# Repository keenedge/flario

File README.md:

# FLARIO

## Windows Dev Config

ESP32 plugin to a local com port. (COM10)

A a TASkSchd task
- At System Startup
- Program: "C:\Program Files (x86)\com0com\hub4com.exe"
- Args: --baud=115200 \\.\COM10 --use-driver=tcp 7000

## MX Linux dev config

/etc/systemd/system/ttyVCOM0

   [Unit]
   Description=ESP32 TCP to TTY Bridge (/dev/ttyVCOM0)
   After=network-online.target
   Wants=network-online.target

   [Service]
   Type=simple
   ExecStart=/usr/bin/socat \
     pty,raw,echo=0,link=/dev/ttyVCOM0,mode=666,b115200 \
     tcp:10.0.0.8:7000,retry=1000000,interval=1
   Restart=always
   RestartSec=1

   [Install]
   WantedBy=multi-user.target

### Restart Service
sudo systemctl daemon-reload
sudo systemctl restart ttyvcom0.service

### Test

   screen /dev/ttyVCOM0

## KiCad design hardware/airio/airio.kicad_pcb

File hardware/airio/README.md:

# airio

KiCad project for the airio carrier board: a Seeed XIAO nRF52840 soldered on
as a castellated module, with a BMP581 barometer, an LSM6DSV16X IMU, a piezo
beeper, a button, a 1S LiPo connector and SWD test pads. Signals follow the
pin map in [docs/airio-parts-and-pinmap.md](../../docs/airio-parts-and-pinmap.md).

Open `airio.kicad_pro` in KiCad 10. All files are saved in the KiCad 10
format. `airio.pdf` is a plot of the current schematic for reading without
KiCad.

| File | Contents |
|---|---|
| `airio.kicad_sch` | Schematic, one A4 sheet |
| `airio.kicad_pcb` | Two-layer board, 1.0 mm thick: layout and routing in progress |
| `airio.kicad_dru` | Custom DRC rules (see PCB below) |
| `airio-top.png` | Render of an earlier placement |
| `airio.kicad_sym` | Project symbols: XIAO nRF52840, BMP581, LSM6DSV16X |
| `airio.pretty/` | Project footprints: `XIAO-nRF52840-SMD`, `Bosch_LGA-10_2x2mm_P0.5mm` |
| `sym-lib-table`, `fp-lib-table` | Add the two project libraries as `airio` |
| `airio.pdf` | Schematic plot |

## ERC

ERC in KiCad 10.0.7 reports 0 errors and 2 warnings. Both warnings are
sensor address straps tied to a supply rail, which is intended:

- U2 (BMP581) SDO to +3V3 selects I2C address 0x47.
- U3 (LSM6DSV16X) SDO/SA0 to GND selects I2C address 0x6A.

Exclude them in the ERC window (right-click, Exclude) if you want a clean run.

## Footprints

- **U1** uses Seeed's `XIAO-nRF52840-SMD` footprint from
  [Seeed-Studio/OPL_Kicad_Library](https://github.com/Seeed-Studio/OPL_Kicad_Library)
  (commit 3be8215, CC-BY-SA-4.0). Pads 1-14 are the castellated edge, 15-18 the
  underside SWD pads (SWDIO, SWCLK, RST, GND), 19-20 the battery pads (BAT+,
  BAT-) and 21-22 NFC1/NFC2. The project symbol's underside pins were
  renumbered to Seeed's order so they land on the right pads.
- **U2** uses `Bosch_LGA-10_2x2mm_P0.5mm`: 10 pads at 0.5 mm pitch, two on the
  pin 1 side and three on each adjacent side, numbered counter-clockwise from
  the top. Pad centres sit 0.775 mm from the body centre, pads are 0.30 x
  0.325 mm. It was cross-checked against four open-source BMP581 footprints,
  since Bosch's datasheet PDF couldn't be read here. Check it against
  section 8 of the datasheet before ordering. The BMP580 uses the same package.

Every symbol pin has a matching footprint pad (checked with KiCad's pcbnew
Python against the netlist).

## Display options

J3 is a cable port for a display breakout (Sharp memory LCD, or an ST7305
adapter). J6 is an on-board 24-pin 0.5 mm FPC for a bare 2.9" 168x384 ST7305
reflective panel (Osptek YDP290H001-V3, Good Display GDTL029T51), with its
seven 1 µF capacitors C6-C12. Both share SCR_CLK, SCR_MOSI, SCR_CS, SCR_DISP
(ST7305 RES) and SCR_DC (D8). Fit one display at a time.

J6's footprint is a placeholder (`Hirose_FH12-24S-0.5SH`): check the pads
against the HCTL HC-FPC-05-09-24RLTAG drawing before layout. The J6 pinout and
capacitor values come from search extracts of the panel spec, not the PDF
itself; confirm them too. `airio.pdf` has not been re-plotted for J6.

## PCB

- **Size:** 54 x 24 mm, two layers, 1.0 mm FR4. SMD parts sit on the top side
  for single-sided JLC reflow. J2-J5 are SMD JST SH, so the
  whole board can be reflowed. The six bare test pads are on the bottom.
- **Placement and routing:** being re-laid out and routed by hand in KiCad (work
  in progress). `airio-top.png` shows the earlier scripted placement, not the
  current layout. The antenna keepout rule area and the custom rules stay.
- **Test pads:** TP1-TP6 are on the bottom in a 2.54 mm row (GND, 3V3, SWDIO,
  SWCLK, RST, VBAT, left to right seen from the top), under the battery, for a
  pogo-pin SWD adapter.
- **DRC:** KiCad 10.0.7 with schematic parity finds no footprint or parity
  errors. `airio.kicad_dru` allows the 0.15 mm pad gaps of ST's LGA-14 land
  pattern, sets a 0.3 mm copper-to-edge clearance, and allows 0.15 mm tracks,
  all within JLC's standard limits.

## Parts

Prices are LCSC, converted at 1.3993 CAD per USD (Bank of Canada, 2026-10-23),
excluding shipping and duty. Stock was read from LCSC's product API on
2026-10-24, on 2026-10-25 for U2, U4 and R3/R4, and on 2026-10-26 for J2-J5. "Each" is the price at LCSC's smallest order quantity.

| Ref | Part | LCSC # | Qty | CAD each | Min order | LCSC stock |
|---|---|---|---|---|---|---|
| U1 | Seeed XIAO nRF52840 (102010448) | [C17209540](https://www.lcsc.com/product-detail/C17209540.html) | 1 | C$15.18 | 1 | 158 |
| U2 | Bosch BMP581 | [C5362283](https://www.lcsc.com/product-detail/C5362283.html) | 1 | C$3.41 | 1 | 7,388 |
| U2 alt | Bosch BMP580 | [C22391138](https://www.lcsc.com/product-detail/C22391138.html) | 1 | C$1.70 | 1 | 14,944 |
| U3 | ST LSM6DSV16XTR | [C5267406](https://www.lcsc.com/product-detail/C5267406.html) | 1 | C$4.75 | 1 | 6,395 |
| J1 | JST S2B-PH-K-S(LF)(SN), 2-pin PH side-entry THT, on the back | [C173752](https://www.lcsc.com/product-detail/C173752.html) | 1 | C$0.056 | 20 | 202,040 |
| J2, J4 | JST SM04B-SRSS-TB(LF)(SN), 4-pin SH side-entry SMD | [C160404](https://www.lcsc.com/product-detail/C160404.html) | 2 | C$0.303 | 5 | 63,590 |
| J3 | JST SM08B-SRSS-TB(LF)(SN), 8-pin SH side-entry SMD | [C160407](https://www.lcsc.com/product-detail/C160407.html) | 1 | C$0.457 | 5 | 194,320 |
| J5 | JST SM02B-SRSS-TB(LF)(SN), 2-pin SH side-entry SMD (buzzer) | [C160402](https://www.lcsc.com/product-detail/C160402.html) | 1 | C$0.187 | 5 | 73,300 |
| SW1 | XKB TS-1187A-B-A-B | [C318884](https://www.lcsc.com/product-detail/C318884.html) | 1 | C$0.03 | 20 | 923,940 |
| C1-C4 | Samsung CL10B104KO8NNNC, 100 nF 16 V X7R 0603 | [C66501](https://www.lcsc.com/product-detail/C66501.html) | 4 | C$0.013 | 50 | 796,150 |
| R1, R2 | UNI-ROYAL 0603WAF4701T5E, 4.7 kΩ 0603 | [C23162](https://www.lcsc.com/product-detail/C23162.html) | 2 | C$0.004 | 100 | 4,646,400 |
| U4 | TI TCA9534PWR I/O expander, TSSOP-16 | [C783615](https://www.lcsc.com/product-detail/C783615.html) | 1 | C$1.31 | 1 | 11,270 |
| R3, R4 | UNI-ROYAL 0603WAF1002T5E, 10 kΩ 0603 | [C25804](https://www.lcsc.com/product-detail/C25804.html) | 2 | C$0.003 | 100 | 567,800 |
| C5 | Samsung CL10B104KO8NNNC, 100 nF 16 V X7R 0603 | [C66501](https://www.lcsc.com/product-detail/C66501.html) | 1 | C$0.013 | 50 | 796,150 |

Ports J2-J4 follow `/mnt/project-files/airio/core-ports-spec.md`: pin 1 is GND on
all of them. J2-J5 are JST SH (1.0 mm) side-entry SMD, so JLC can reflow them; they
need to sit at the board edge, and SH leads are best bought pre-crimped. J4 matches the
Qwiic / STEMMA QT pinout. The buzzer is off-board on J5. The NFC pads sit inside the
antenna keepout, so they are unused. U4, a TCA9534 I2C expander at 0x20, carries BTN
(P3), BARO_INT (P0), SCR_DISP (P2) and IMU_INT1 (P1); its INT output on D5 wakes the
XIAO from System OFF. See the pin map for the XIAO pin assignment.

C1-C4 were changed from C1591 to C66501 because C1591 shows 0 stock at LCSC.
The BMP581 is back in stock at LCSC (2026-10-25); the BMP580 still fits the same footprint as a fallback.

## J1 on the back

J1 is a through-hole JST PH (S2B-PH-K-S) mounted on the bottom side, so the
battery lead runs along the back. Hand solder it from the top after JLC's
single-sided assembly, and mark it "do not place" in the JLC BOM. Its pins
poke about 1.5 mm through the top side, so keep those spots clear.

## Still to do before ordering

- Check J1's polarity against the LiPo you'll use. Pin 1 is VBAT. JST PH
  battery packs are not consistent about which side is red.
- Check the BMP581 footprint against section 8 of the datasheet.

To point the KiCad MCP server at this project, set
`KICAD_MCP_PROJECT_DIR=hardware/airio` or ask Claude to call `kicad_set_project`.

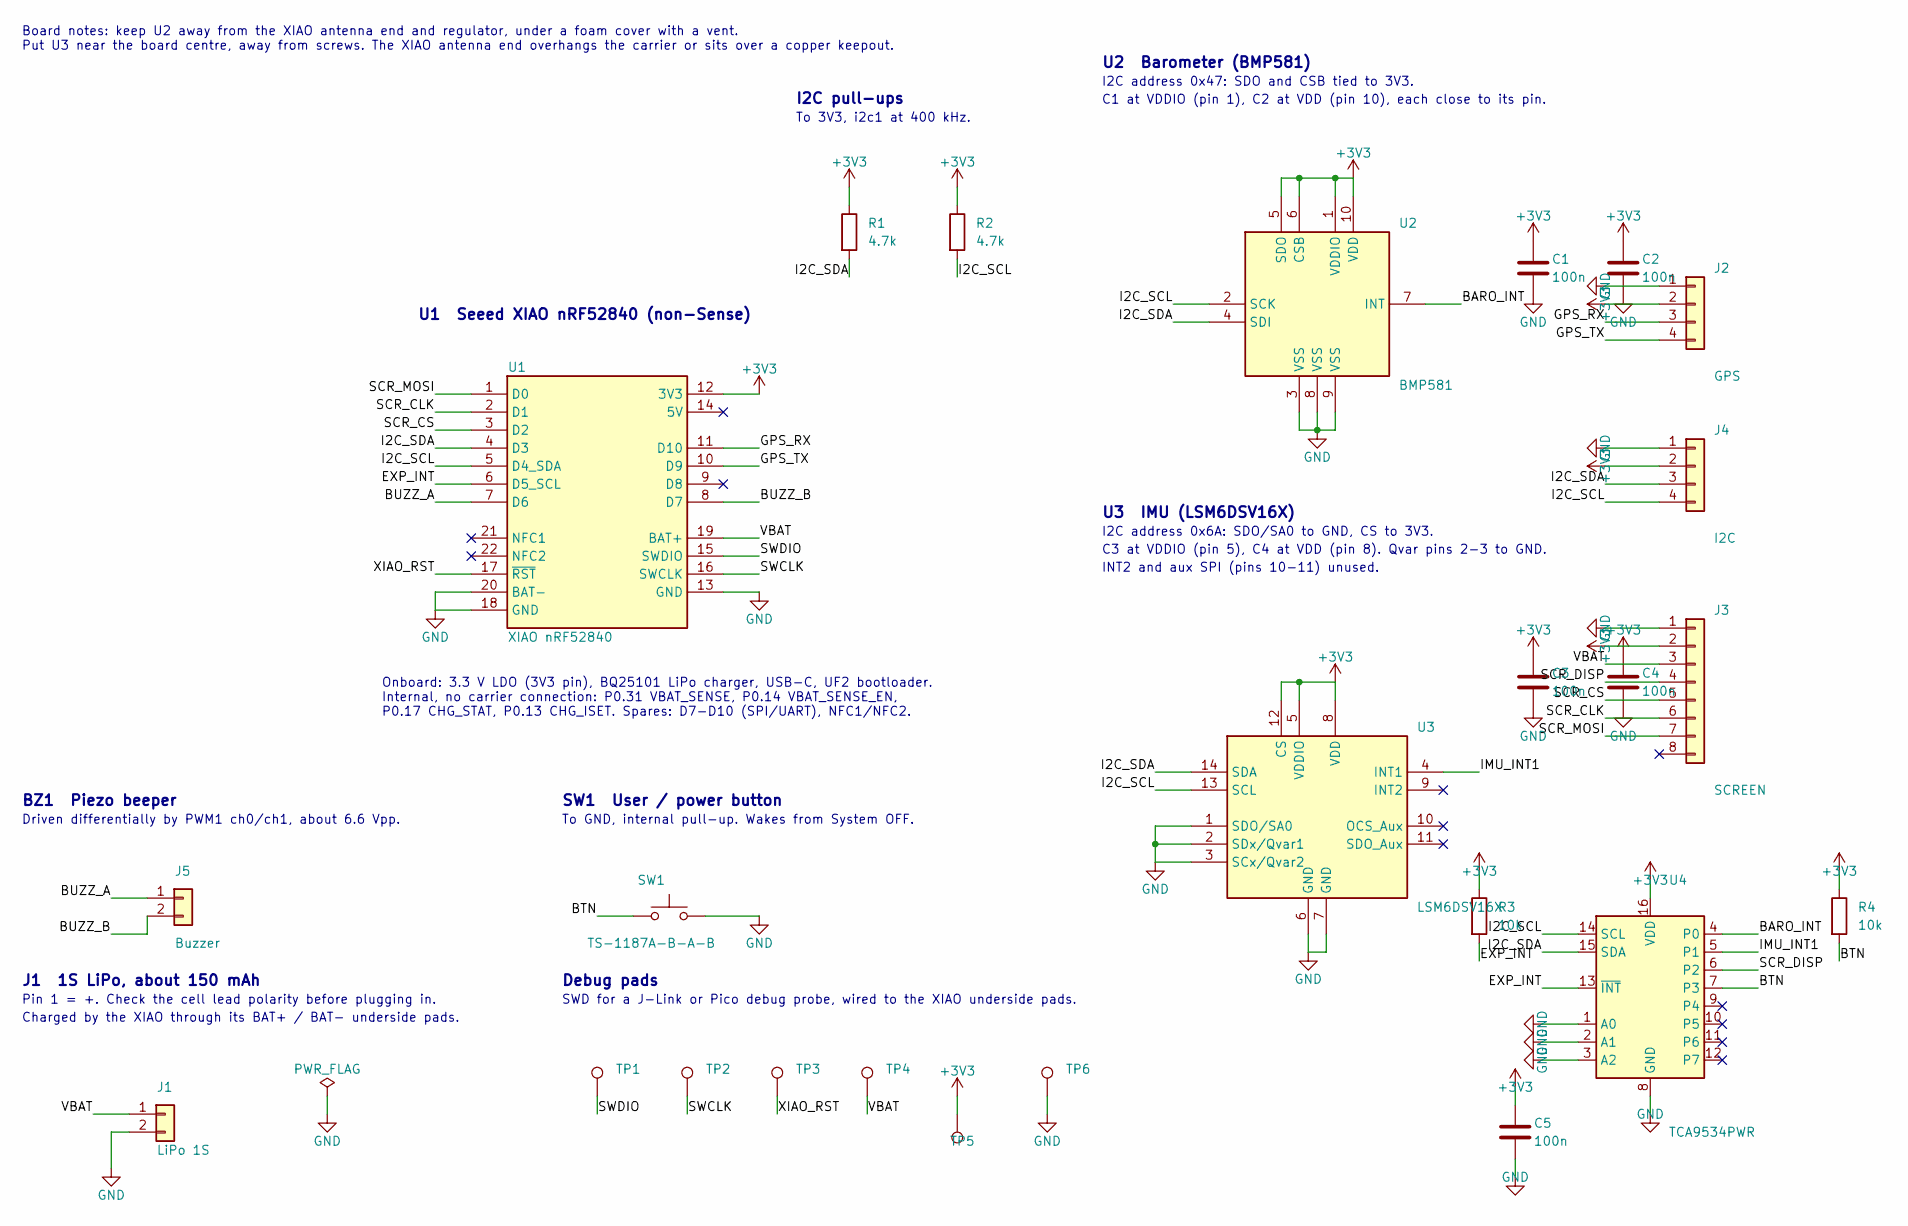
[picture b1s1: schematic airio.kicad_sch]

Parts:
C1, C2, C3, C4: 100n; C_0603_1608Metric; LCSC C66501
C5: 100n; C_0603_1608Metric; MPN Samsung CL10B104KO8NNNC; LCSC C66501
J1: LiPo 1S; JST_PH_S2B-PH-K_1x02_P2.00mm_Horizontal; MPN JST S2B-PH-K-S(LF)(SN); LCSC C173752
J2: GPS; JST_SH_SM04B-SRSS-TB_1x04-1MP_P1.00mm_Horizontal; MPN JST SM04B-SRSS-TB(LF)(SN); LCSC C160404
J3: SCREEN; JST_SH_SM08B-SRSS-TB_1x08-1MP_P1.00mm_Horizontal; MPN JST SM08B-SRSS-TB(LF)(SN); LCSC C160407
J4: I2C; JST_SH_SM04B-SRSS-TB_1x04-1MP_P1.00mm_Horizontal; MPN JST SM04B-SRSS-TB(LF)(SN); LCSC C160404
J5: Buzzer; JST_SH_SM02B-SRSS-TB_1x02-1MP_P1.00mm_Horizontal; MPN JST SM02B-SRSS-TB(LF)(SN); LCSC C160402
R1, R2: 4.7k; R_0603_1608Metric; LCSC C23162
R3, R4: 10k; R_0603_1608Metric; MPN UNI-ROYAL 0603WAF1002T5E; LCSC C25804
SW1: TS-1187A-B-A-B; SW_Push_1P1T_XKB_TS-1187A; LCSC C318884
TP1: SWDIO; TestPoint_Pad_D1.0mm
TP2: SWCLK; TestPoint_Pad_D1.0mm
TP3: XIAO_RST; TestPoint_Pad_D1.0mm
TP4: VBAT; TestPoint_Pad_D1.0mm
TP5: +3V3; TestPoint_Pad_D1.0mm
TP6: GND; TestPoint_Pad_D1.0mm
U1: XIAO nRF52840; XIAO-nRF52840-SMD; MPN Seeed 102010448; LCSC C17209540
U2: BMP581; Bosch_LGA-10_2x2mm_P0.5mm; LCSC C5362283
U3: LSM6DSV16X; LGA-14_3x2.5mm_P0.5mm_LayoutBorder3x4y; MPN LSM6DSV16XTR; LCSC C5267406
U4: TCA9534PWR; TSSOP-16_4.4x5mm_P0.65mm; MPN TI TCA9534PWR; LCSC C783615

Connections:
+3V3: C1.1, C2.1, C3.1, C4.1, C5.1, J2.2, J3.2, J4.2, R1.1, R2.1, R3.1, R4.1, TP5.1 (1_1), U1.12 (3V3), U2.1 (VDDIO), U2.5 (SDO), U2.6 (CSB), U2.10 (VDD), U3.5 (VDDIO), U3.8 (VDD), U3.12 (CS), U4.16 (VDD)
/BARO_INT: U2.7 (INT), U4.4 (P0)
/BTN: R4.2, SW1.1, U4.7 (P3); also elsewhere on the board
/BUZZ_A: J5.1, U1.7 (D6)
/BUZZ_B: J5.2, U1.8 (D7)
/EXP_INT: R3.2, U1.6 (D5_SCL), U4.13 (~INT)
/GPS_RX: J2.3, U1.11 (D10)
/GPS_TX: J2.4, U1.10 (D9)
/I2C_SCL: J4.4, R2.2, U1.5 (D4_SDA), U2.2 (SCK), U3.13 (SCL), U4.14 (SCL)
/I2C_SDA: J4.3, R1.2, U1.4 (D3), U2.4 (SDI), U3.14 (SDA), U4.15 (SDA)
/IMU_INT1: U3.4 (INT1), U4.5 (P1)
/SCR_CLK: J3.6, U1.2 (D1)
/SCR_CS: J3.5, U1.3 (D2)
/SCR_DISP: J3.4, U4.6 (P2)
/SCR_MOSI: J3.7, U1.1 (D0)
/SWCLK: TP2.1 (1_1), U1.16 (SWCLK)
/SWDIO: TP1.1, U1.15 (SWDIO)
/VBAT: J1.1, J3.3, TP4.1 (1_1), U1.19 (BAT+)
/XIAO_RST: TP3.1 (1_1), U1.17 (~RST)
GND: C1.2, C2.2, C3.2, C4.2, C5.2, J1.2, J2.1, J3.1, J4.1, SW1.2, TP6.1 (1_1), U1.13 (GND), U1.18 (GND), U1.20 (BAT-), U2.3 (VSS), U2.8 (VSS), U2.9 (VSS), U3.1 (SDO/SA0), U3.2 (SDx/Qvar1), U3.3 (SCx/Qvar2), U3.6 (GND), U3.7 (GND), U4.1 (A0), U4.2 (A1), U4.3 (A2), U4.8 (GND); also elsewhere on the board

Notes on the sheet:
I2C address 0x47: SDO and CSB tied to 3V3.
U1 Seeed XIAO nRF52840 (non-Sense)
SWD for a J-Link or Pico debug probe, wired to the XIAO underside pads.
J1 1S LiPo, about 150 mAh
SW1 User / power button
To GND, internal pull-up. Wakes from System OFF.
Debug pads
To 3V3, i2c1 at 400 kHz.
I2C address 0x6A: SDO/SA0 to GND, CS to 3V3.
C3 at VDDIO (pin 5), C4 at VDD (pin 8). Qvar pins 2-3 to GND.
BZ1 Piezo beeper
I2C pull-ups
Pin 1 = +. Check the cell lead polarity before plugging in.
Board notes: keep U2 away from the XIAO antenna end and regulator, under a foam cover with a vent. Put U3 near the board centre, away from screws. The XIAO antenna end overhangs the carrier or sits over a copper keepout.
Driven differentially by PWM1 ch0/ch1, about 6.6 Vpp.
U3 IMU (LSM6DSV16X)
Onboard: 3.3 V LDO (3V3 pin), BQ25101 LiPo charger, USB-C, UF2 bootloader. Internal, no carrier connection: P0.31 VBAT_SENSE, P0.14 VBAT_SENSE_EN, P0.17 CHG_STAT, P0.13 CHG_ISET. Spares: D7-D10 (SPI/UART), NFC1/NFC2.
U2 Barometer (BMP581)
INT2 and aux SPI (pins 10-11) unused.
C1 at VDDIO (pin 1), C2 at VDD (pin 10), each close to its pin.
Charged by the XIAO through its BAT+ / BAT- underside pads.

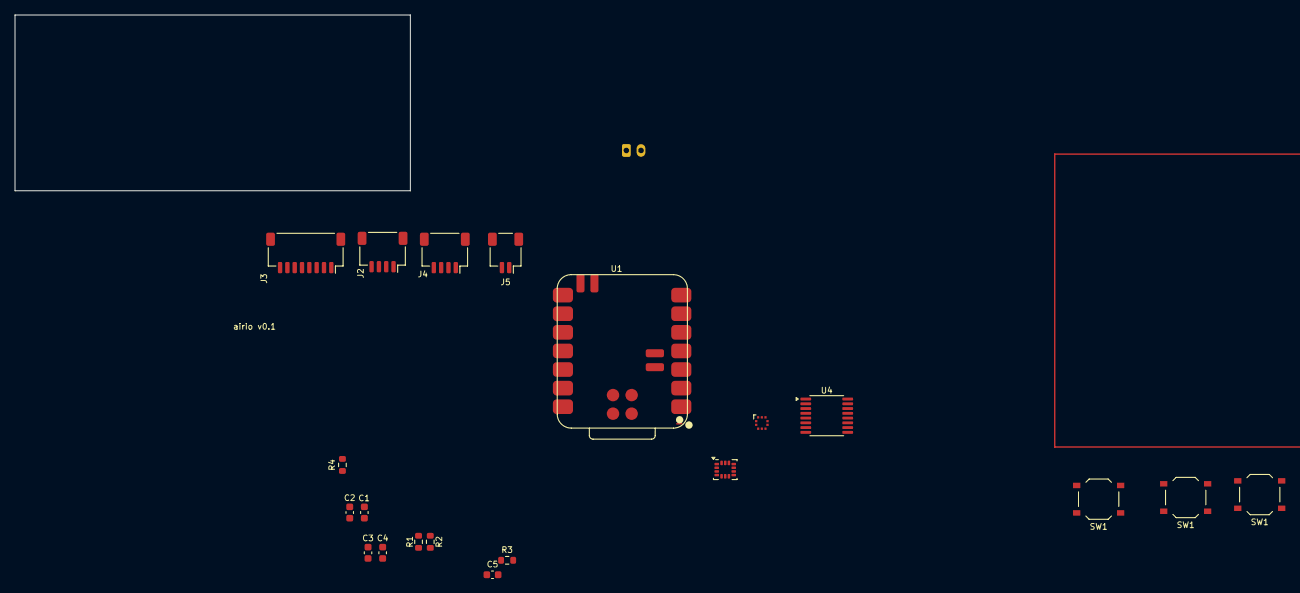
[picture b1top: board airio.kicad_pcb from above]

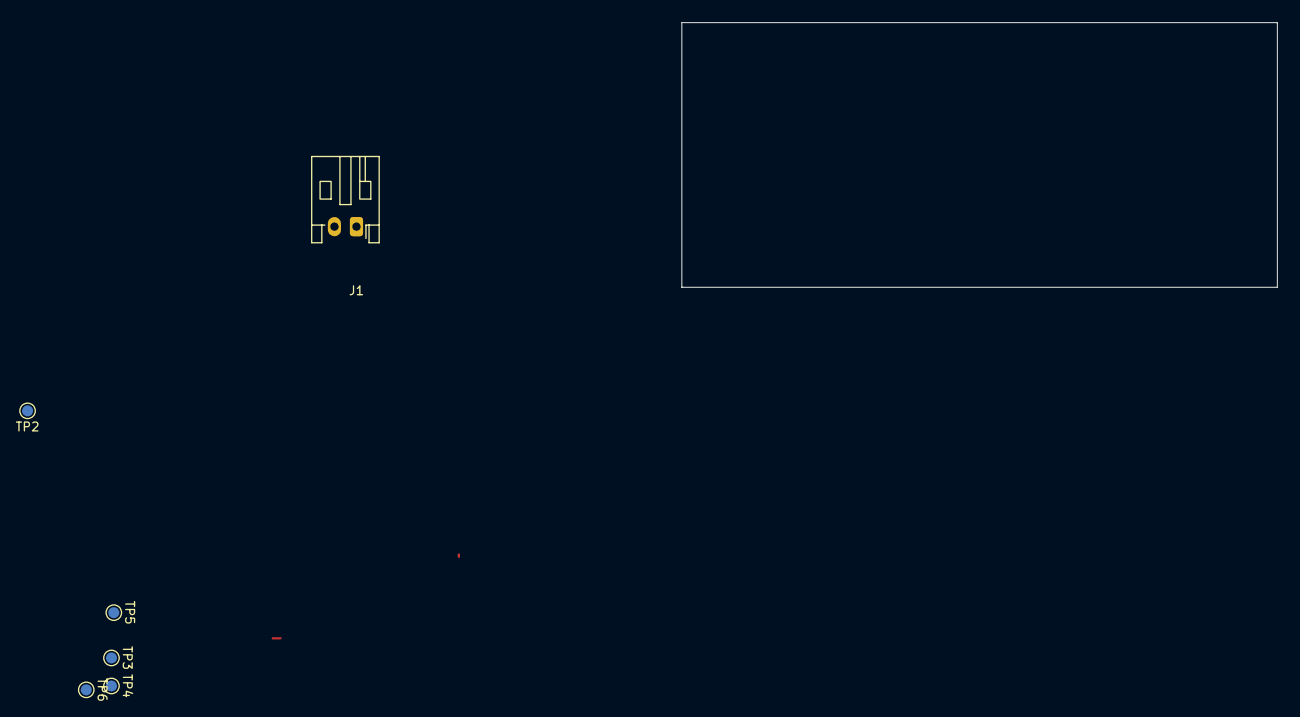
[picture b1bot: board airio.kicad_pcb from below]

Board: 2 copper layers, 54.0 x 24.0 mm, 26 parts (6 on the bottom side), 19 nets.

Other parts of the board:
SW1#2, SW1#3: TS-1187A-B-A-B; SW_Push_1P1T_XKB_TS-1187A

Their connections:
/BTN: SW1#2.1, SW1#3.1; also elsewhere on the board
GND: SW1#2.2, SW1#3.2; also elsewhere on the board

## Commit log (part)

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2026-02-02 Update README with Windows and MX Linux dev config
    Added configuration instructions for Windows and MX Linux development environments.
2026-02-02 Update headings in README.md for consistency
2026-02-02 Update project name to 'FLARIO'
2026-02-25 First version of the MS5611 driver component
2026-02-28 few changes to compile paths and file name.
2026-02-28 added bno library,
2026-03-01 Finally both sensors working.
2026-03-07 Loads of changes. Prett good notification mechanism now. reading look close,
2026-03-09 temp branch for tuiny test and frequency reporting
2026-03-09 Moved working imu code to the imu_task
2026-03-10 working example for large BB
2026-03-11 working example for large BB - revised
2026-03-17 Added oled display
2026-03-17 Added 3 pages and a QNH Variable controlled by the encoder
2026-03-17 chnaged partitions so qnh is not overwritten
2026-06-28 Add pull-up and pull-down resistor selection guide
2026-06-28 Add decoupling and bypass capacitor selection guide
2026-06-28 Add Flario parts list with SMT speaker
2026-06-28 Expand Flario locked and required parts list

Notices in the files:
parts and their libraries:
Seeed Studio XIAO nRF52840, surface-mount castellated, with underside SWD (15-18) and battery (19-20) pads. From Seeed-Studio/OPL_Kicad_Library commit 3be8215, CC-BY-SA-4.0.
